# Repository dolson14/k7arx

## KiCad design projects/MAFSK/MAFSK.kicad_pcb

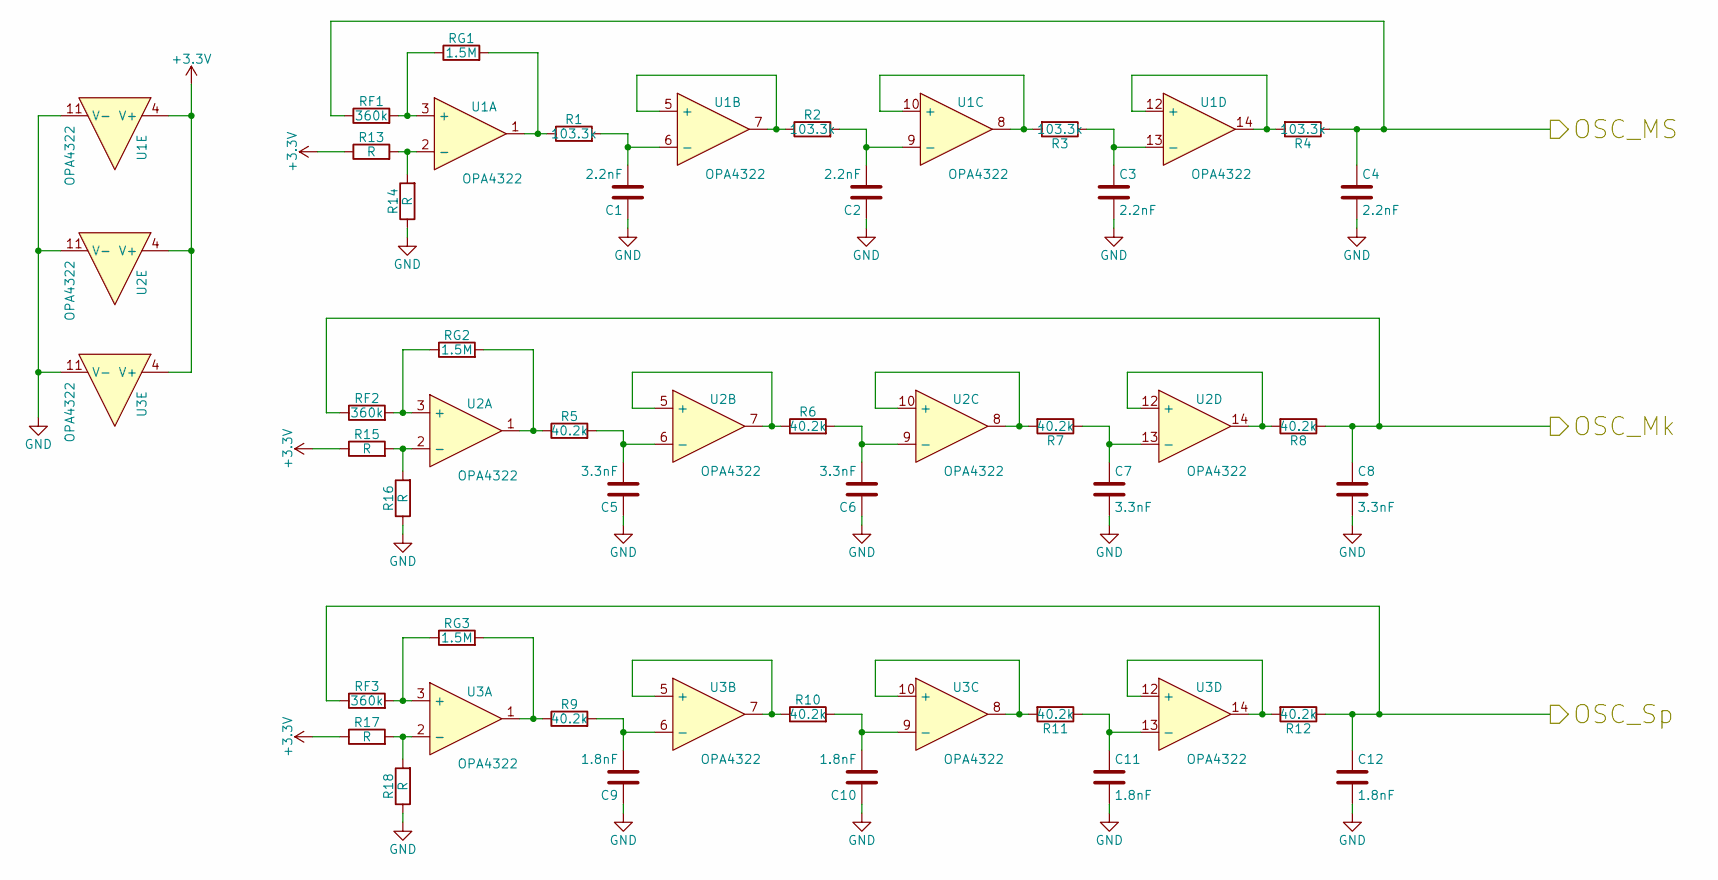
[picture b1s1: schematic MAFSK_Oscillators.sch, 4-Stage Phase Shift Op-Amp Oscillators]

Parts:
C1, C2, C3, C4: 2.2nF; C_1206_HandSoldering
C5, C6, C7, C8: 3.3nF; C_1206_HandSoldering
C9, C10, C11, C12: 1.8nF; C_1206_HandSoldering
R1, R2, R3, R4: 103.3k; R_1206_HandSoldering
R5, R6, R7, R8, R9, R10, R11, R12: 40.2k; R_1206_HandSoldering
R13, R14, R15, R16, R17, R18: R; R_1206_HandSoldering
RF1, RF2, RF3: 360k; R_1206_HandSoldering
RG1, RG2, RG3: 1.5M; R_1206_HandSoldering
U1, U2, U3: OPA4322; PW-14

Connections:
+3V3: R13.1, R15.1, R17.1, U1.4 (V+), U2.4 (V+), U3.4 (V+); also elsewhere on the board
/Oscillators/OSC_MS: C4.1, R4.1, RF1.1; also elsewhere on the board
/Oscillators/OSC_Mk: C8.1, R8.1, RF2.1; also elsewhere on the board
/Oscillators/OSC_Sp: C12.1, R12.1, RF3.1; also elsewhere on the board
GND: C1.1, C2.1, C3.2, C4.2, C5.1, C6.1, C7.2, C8.2, C9.1, C10.1, C11.2, C12.2, R14.1, R16.1, R18.1, U1.11 (V-), U2.11 (V-), U3.11 (V-); also elsewhere on the board
unnamed: C1.2, R1.2, U1.6 (-)
unnamed: C2.2, R2.2, U1.9 (-)
unnamed: C3.1, R3.1, U1.13 (-)
unnamed: C5.2, R5.2, U2.6 (-)
unnamed: C6.2, R6.2, U2.9 (-)
unnamed: C7.1, R7.1, U2.13 (-)
unnamed: C9.2, R9.2, U3.6 (-)
unnamed: C10.2, R10.2, U3.9 (-)
unnamed: C11.1, R11.1, U3.13 (-)
unnamed: R1.1, RG1.2, U1.1
unnamed: R2.1, U1.5 (+), U1.7
unnamed: R3.2, U1.8, U1.10 (+)
unnamed: R4.2, U1.12 (+), U1.14
unnamed: R5.1, RG2.2, U2.1
unnamed: R6.1, U2.5 (+), U2.7
unnamed: R7.2, U2.8, U2.10 (+)
unnamed: R8.2, U2.12 (+), U2.14
unnamed: R9.1, RG3.2, U3.1
unnamed: R10.1, U3.5 (+), U3.7
unnamed: R11.2, U3.8, U3.10 (+)
unnamed: R12.2, U3.12 (+), U3.14
unnamed: R13.2, R14.2, U1.2 (-)
unnamed: R15.2, R16.2, U2.2 (-)
unnamed: R17.2, R18.2, U3.2 (-)
unnamed: RF1.2, RG1.1, U1.3 (+)
unnamed: RF2.2, RG2.1, U2.3 (+)
unnamed: RF3.2, RG3.1, U3.3 (+)

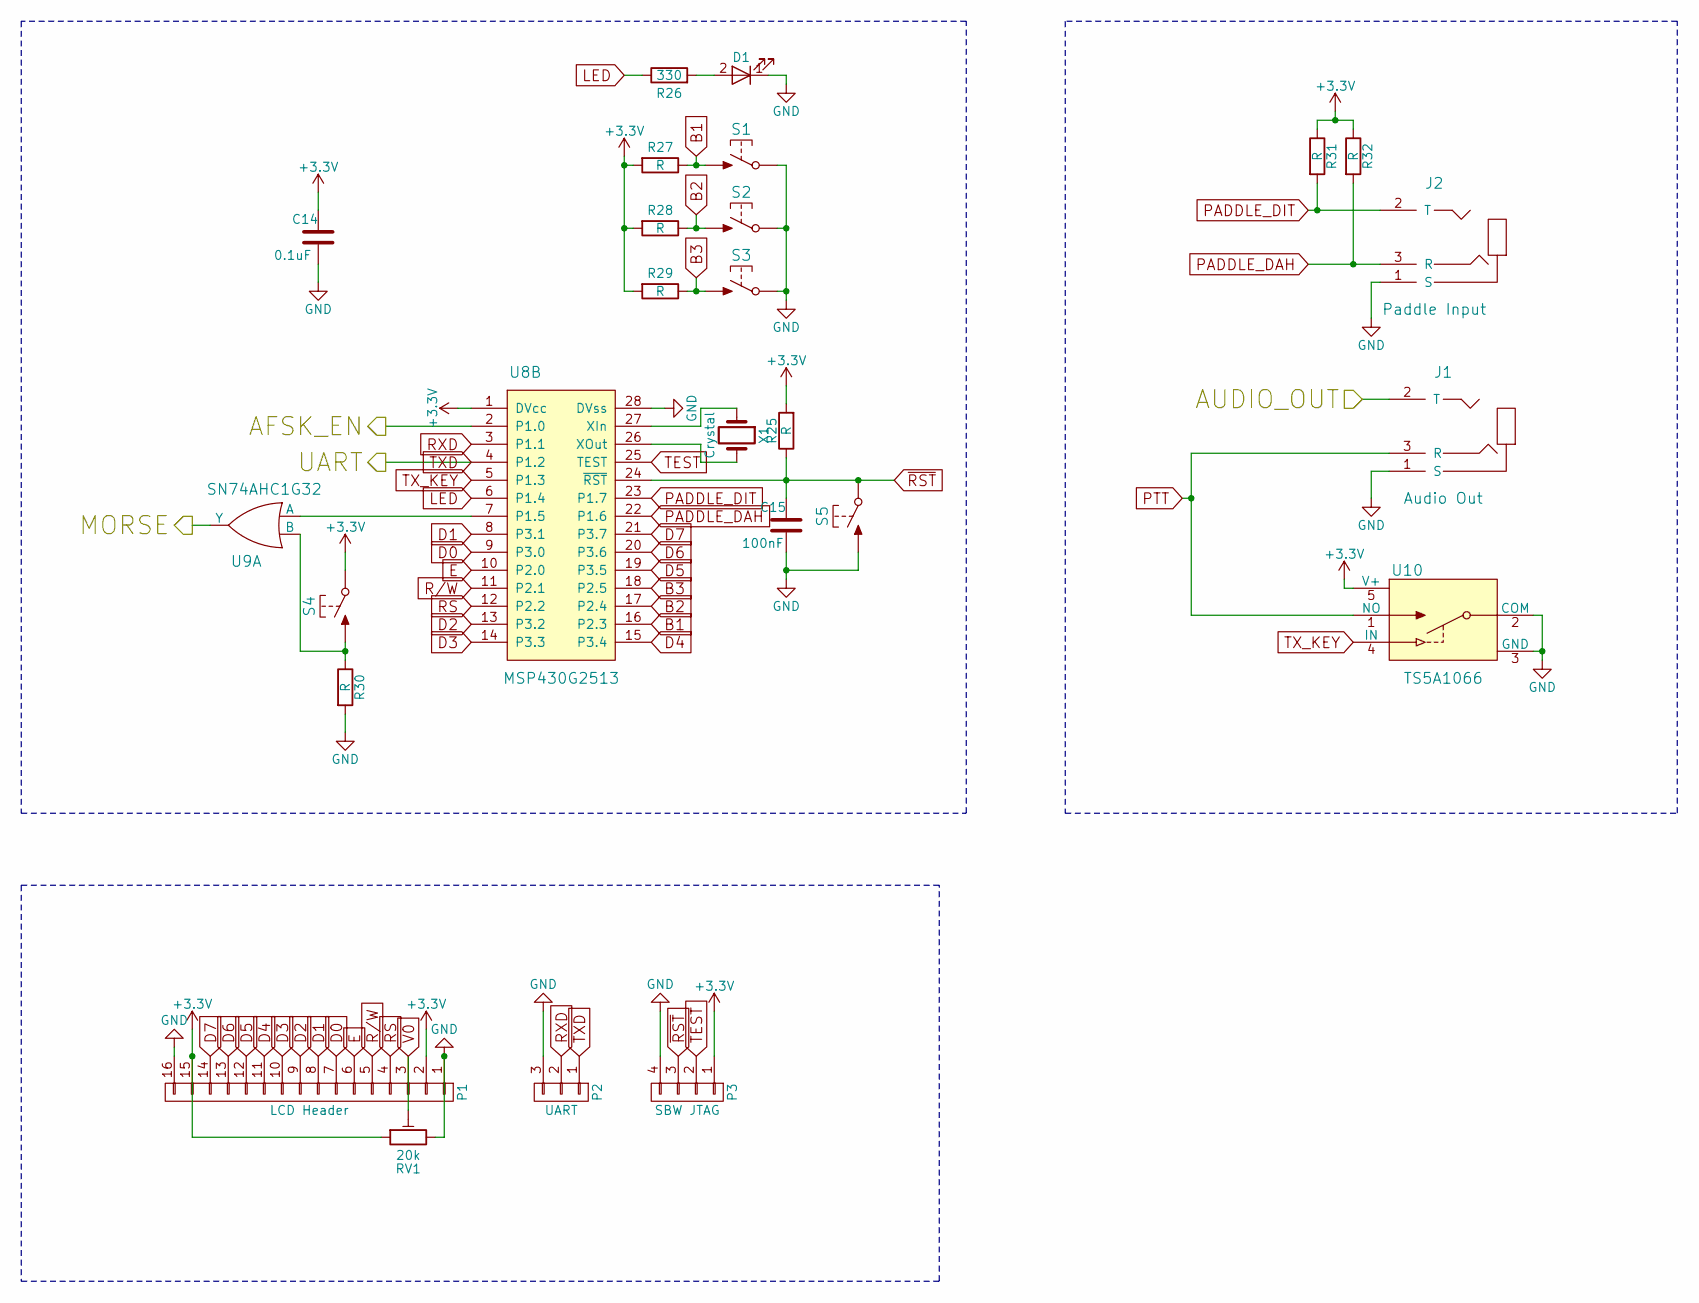
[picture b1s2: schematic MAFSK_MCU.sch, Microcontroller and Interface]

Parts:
C14: 0.1uF; C_1206_HandSoldering
C15: 100nF; C_1206_HandSoldering
D1: LED; LED-0805
J1: Audio Out; Jack-TRS-SJ1-3523N
J2: Paddle Input; Jack-TRS-SJ1-3523N
P1: LCD Header; LCD-1602A
P2: UART; Pin_Header_Straight_1x03
P3: SBW JTAG; Pin_Header_Straight_1x04
R25, R27, R28, R29, R30, R31, R32: R; R_1206_HandSoldering
R26: 330; R_1206_HandSoldering
RV1: 20k; POT-3352T
S1, S2, S3, S4: TactileSwitch_NO; SPST-D6xxx
S5: TactileSwitch_NO; SPST-EVQ2
U8: MSP430G2513; PW-28
U9: SN74AHC1G32; DBV
U10: TS5A1066; DBV
X1: Crystal; XTAL-CMR200T

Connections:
+3V3: C14.1, P1.2, P1.15, P3.1, R25.2, R27.2, R28.2, R29.2, R31.1, R32.1, RV1.1, S4.2 (COM), U8.1 (DVcc), U10.5 (V+); also elsewhere on the board
/Microcontroller/AFSK_EN: U8.2 (P1.0); also elsewhere on the board
/Microcontroller/AUDIO_OUT: J1.2 (T); also elsewhere on the board
/Microcontroller/MORSE: U9.4 (Y); also elsewhere on the board
B1: R27.1, S1.1 (NO), U8.16 (~RST)
B2: R28.1, S2.1 (NO), U8.17 (TEST)
B3: R29.1, S3.1 (NO), U8.18 (XOut)
D0: P1.7, U8.9 (P2.1)
D1: P1.8, U8.8 (P2.0)
D2: P1.9, U8.13 (P2.5)
D3: P1.10, U8.14 (P1.6)
D4: P1.11, U8.15 (P1.7)
D5: P1.12, U8.19 (XIn)
D6: P1.13, U8.20 (DVss)
D7: P1.14, U8.21 (P3.7)
E: P1.6, U8.10 (P2.2)
GND: C14.2, C15.2, D1.1 (K), J1.1 (S), J2.1 (S), P1.1, P1.16, P2.3, P3.4, R30.2, RV1.3, S1.2 (COM), S2.2 (COM), S3.2 (COM), S5.1 (NO), U8.28 (DVss), U10.2 (COM), U10.3 (GND); also elsewhere on the board
LED: R26.1, U8.6 (P1.4)
unnamed: D1.2 (A), R26.2
unnamed: R30.1, S4.1 (NO), U9.2 (B)
unnamed: U8.7 (P1.5), U9.1 (A)
unnamed: U8.26 (XOut), X1.2
unnamed: U8.27 (XIn), X1.1
PADDLE_DAH: J2.3 (R), R32.2, U8.22 (P1.6)
PADDLE_DIT: J2.2 (T), R31.2, U8.23 (P1.7)
PTT: J1.3 (R), U10.1 (NO)
R/W: P1.5, U8.11 (P2.3)
RS: P1.4, U8.12 (P2.4)
RXD: P2.2, U8.3 (P1.1)
TEST: P3.2, U8.25 (TEST)
TXD: P2.1, U8.4 (P1.2); also elsewhere on the board
TX_KEY: U8.5 (P1.3), U10.4 (IN)
V0: P1.3, RV1.2
~RST: C15.1, P3.3, R25.1, S5.2 (COM), U8.24 (~RST)

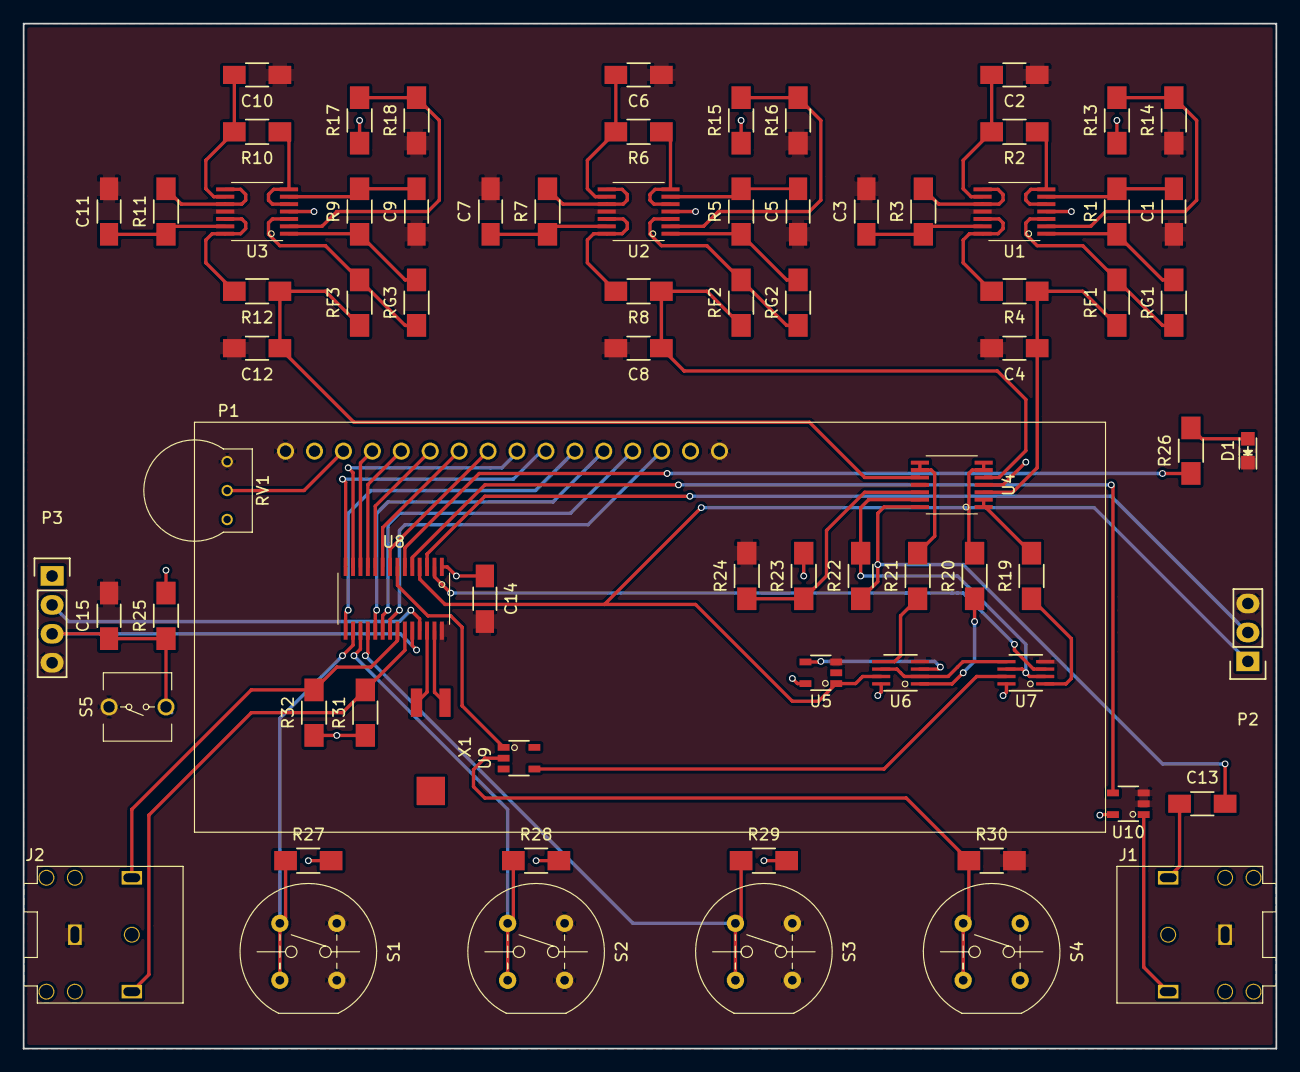
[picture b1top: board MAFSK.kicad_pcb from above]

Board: 2 copper layers, 110.0 x 90.0 mm, 76 parts (0 on the bottom side), 75 nets.

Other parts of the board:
C13: C; C_1206_HandSoldering
R19, R20, R21, R22, R23, R24: R; R_1206_HandSoldering
U4: OPA4322; PW-14
U5: SN74AHC1G14; DBV
U6, U7: TS5A2066; DCT

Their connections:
+3V3: R23.2, U4.4, U5.5, U6.8, U7.8; also elsewhere on the board
/Microcontroller/AFSK_EN: U7.3; also elsewhere on the board
/Microcontroller/AUDIO_OUT: C13.1; also elsewhere on the board
/Microcontroller/MORSE: U7.7; also elsewhere on the board
/Oscillators/OSC_MS: U4.3; also elsewhere on the board
/Oscillators/OSC_Mk: U4.5; also elsewhere on the board
/Oscillators/OSC_Sp: U4.10; also elsewhere on the board
GND: R24.2, U4.11, U5.3, U6.4, U7.4; also elsewhere on the board
unnamed: C13.2, R22.1, U4.14
unnamed: R19.1, U7.1
unnamed: R19.2, U4.1, U4.2
unnamed: R20.1, U6.1
unnamed: R20.2, U4.6, U4.7
unnamed: R21.1, U6.5
unnamed: R21.2, U4.8, U4.9
unnamed: R22.2, U4.13, U7.2, U7.6
unnamed: R23.1, R24.1, U4.12
unnamed: U5.4, U6.3
unnamed: U6.2, U6.6, U7.5
TXD: U5.1, U6.7; also elsewhere on the board

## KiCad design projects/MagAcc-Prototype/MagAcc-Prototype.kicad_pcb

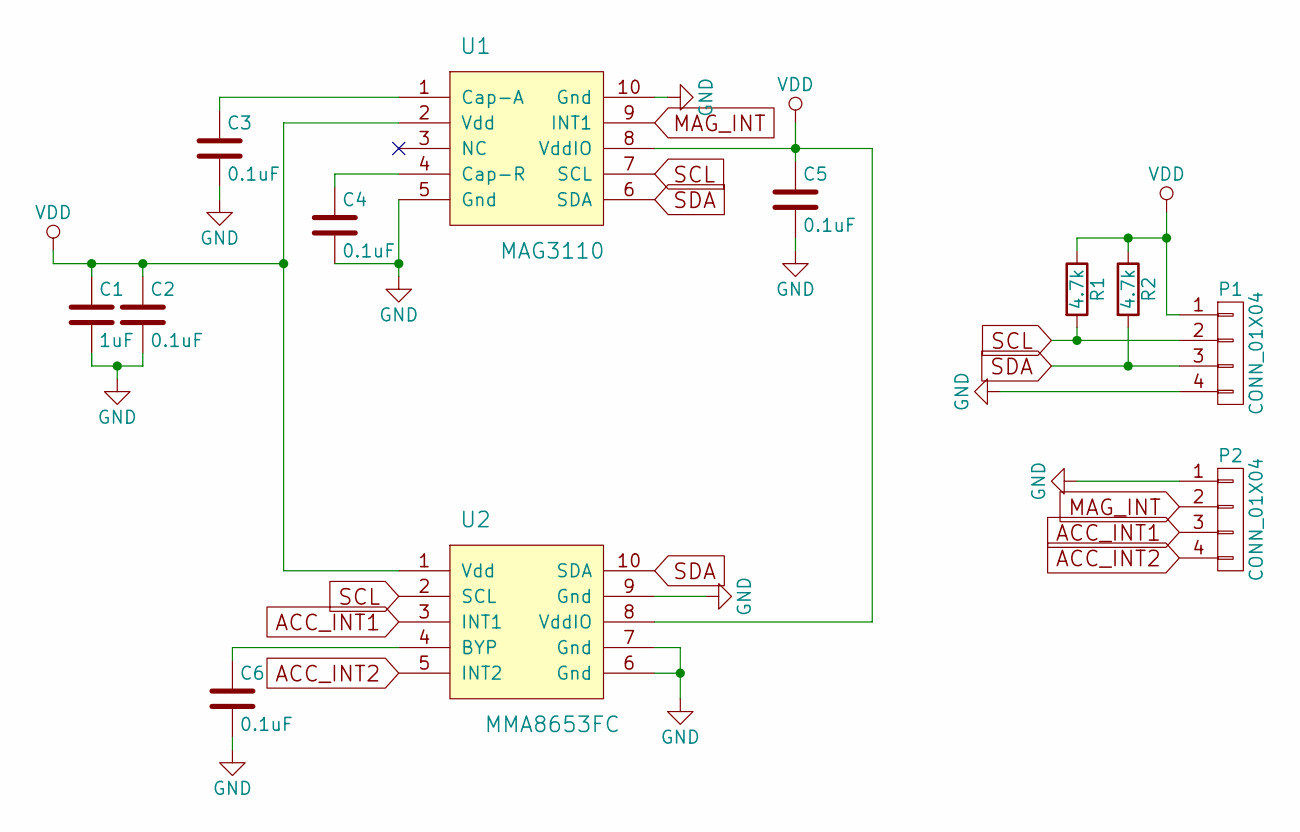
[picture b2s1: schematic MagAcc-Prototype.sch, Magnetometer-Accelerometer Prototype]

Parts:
C1: 1uF; C_1206_HandSoldering
C2, C3, C4, C5, C6: 0.1uF; C_1206_HandSoldering
P1, P2: CONN_01X04; Pin_Header_Straight_1x04
R1, R2: 4.7k; R_1206_HandSoldering
U1: MAG3110; DFN-10-HS
U2: MMA8653FC; DFN-10-HS

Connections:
ACC_INT1: P2.3, U2.3 (INT1)
ACC_INT2: P2.4, U2.5 (INT2)
GND: C1.2, C2.2, C3.2, C4.2, C5.2, C6.2, P1.4, P2.1, U1.5 (Gnd), U1.10 (Gnd), U2.6 (Gnd), U2.7 (Gnd), U2.9 (Gnd)
MAG_INT: P2.2, U1.9 (INT1)
unnamed: C3.1, U1.1 (Cap-A)
unnamed: C4.1, U1.4 (Cap-R)
unnamed: C6.1, U2.4 (BYP)
SCL: P1.2, R1.2, U1.7 (SCL), U2.2 (SCL)
SDA: P1.3, R2.2, U1.6 (SDA), U2.10 (SDA)
VDD: C1.1, C2.1, C5.1, P1.1, R1.1, R2.1, U1.2 (Vdd), U1.8 (VddIO), U2.1 (Vdd), U2.8 (VddIO)

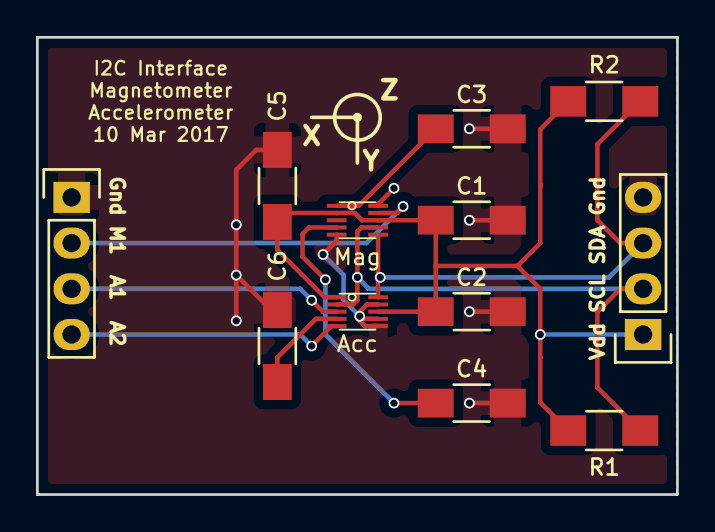
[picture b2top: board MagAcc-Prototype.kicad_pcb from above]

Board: 2 copper layers, 35.6 x 25.4 mm, 12 parts (0 on the bottom side), 10 nets.

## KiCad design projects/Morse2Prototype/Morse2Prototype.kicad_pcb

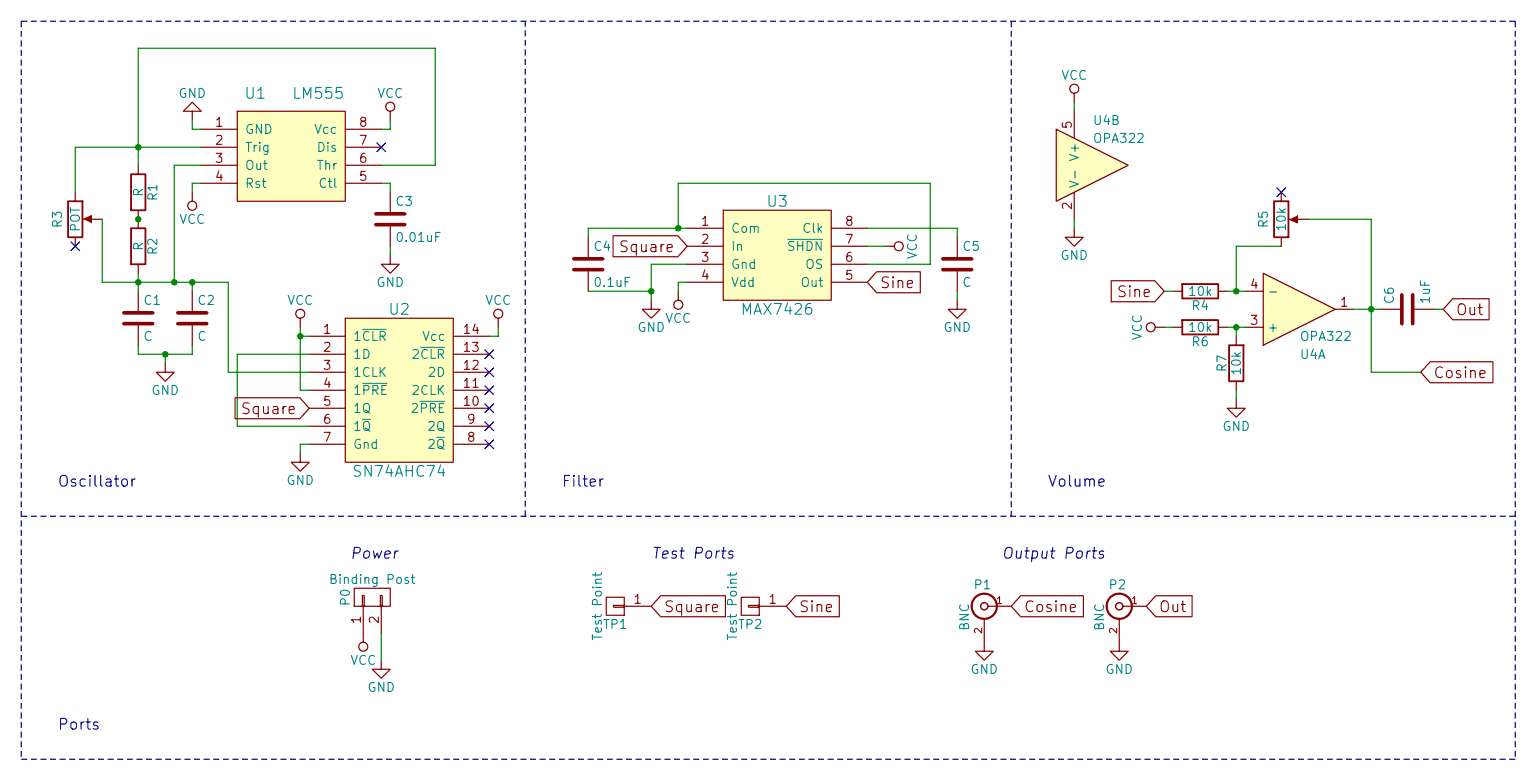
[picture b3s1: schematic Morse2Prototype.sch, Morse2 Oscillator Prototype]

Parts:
C1, C2, C5: C; C_Disc_D6_P5
C3: 0.01uF; C_Disc_D6_P5
C4: 0.1uF; C_Disc_D6_P5
C6: 1uF; C_Radial_D5_L11_P2.5
P0: Binding Post; Pin_Header_Straight_1x02
P1, P2: BNC; SMA_Board_Edge
R1, R2: R; Resistor_Horizontal_RM10mm
R3: POT; Resistor_Horizontal_RM10mm
R4, R5, R6, R7: 10k; Resistor_Horizontal_RM10mm
TP1, TP2: Test Point; Pin_Header_Straight_1x01
U1: LM555; DIP-8_W7.62mm_LongPads
U2: SN74AHC74; DIP-14_W7.62mm_LongPads
U3: MAX7426; DIP-8_W7.62mm_LongPads
U4: OPA322; DIP-8_W7.62mm_LongPads

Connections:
Cosine: C6.1, P1.1 (In), R5.2, U4.1
GND: C1.2, C2.2, C3.2, C4.2, C5.2, P0.2, P1.2 (Ext), P2.2 (Ext), R7.1, U1.1 (GND), U2.7 (Gnd), U3.3 (Gnd), U4.2 (V-)
unnamed: C1.1, C2.1, R2.2, R3.2, U1.3 (Out), U2.3 (1CLK)
unnamed: C3.1, U1.5 (Ctl)
unnamed: C4.1, U3.1 (Com), U3.6 (OS)
unnamed: C5.1, U3.8 (Clk)
unnamed: R1.1, R3.1, U1.2 (Trig), U1.6 (Thr)
unnamed: R1.2, R2.1
unnamed: R4.1, R5.1, U4.4 (-)
unnamed: R6.1, R7.2, U4.3 (+)
unnamed: U2.2 (1D), U2.6 (1~Q)
Out: C6.2, P2.1 (In)
Sine: R4.2, TP2.1, U3.5 (Out)
Square: TP1.1, U2.5 (1Q), U3.2 (In)
VCC: P0.1, R6.2, U1.4 (Rst), U1.8 (Vcc), U2.1 (1~CLR), U2.4 (1~PRE), U2.14 (Vcc), U3.4 (Vdd), U3.7 (~SHDN), U4.5 (V+)

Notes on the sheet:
Oscillator
Filter
Volume
Ports
Test Ports
Output Ports
Power

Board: 2 copper layers, 22 parts (0 on the bottom side), 15 nets, no tracks yet.

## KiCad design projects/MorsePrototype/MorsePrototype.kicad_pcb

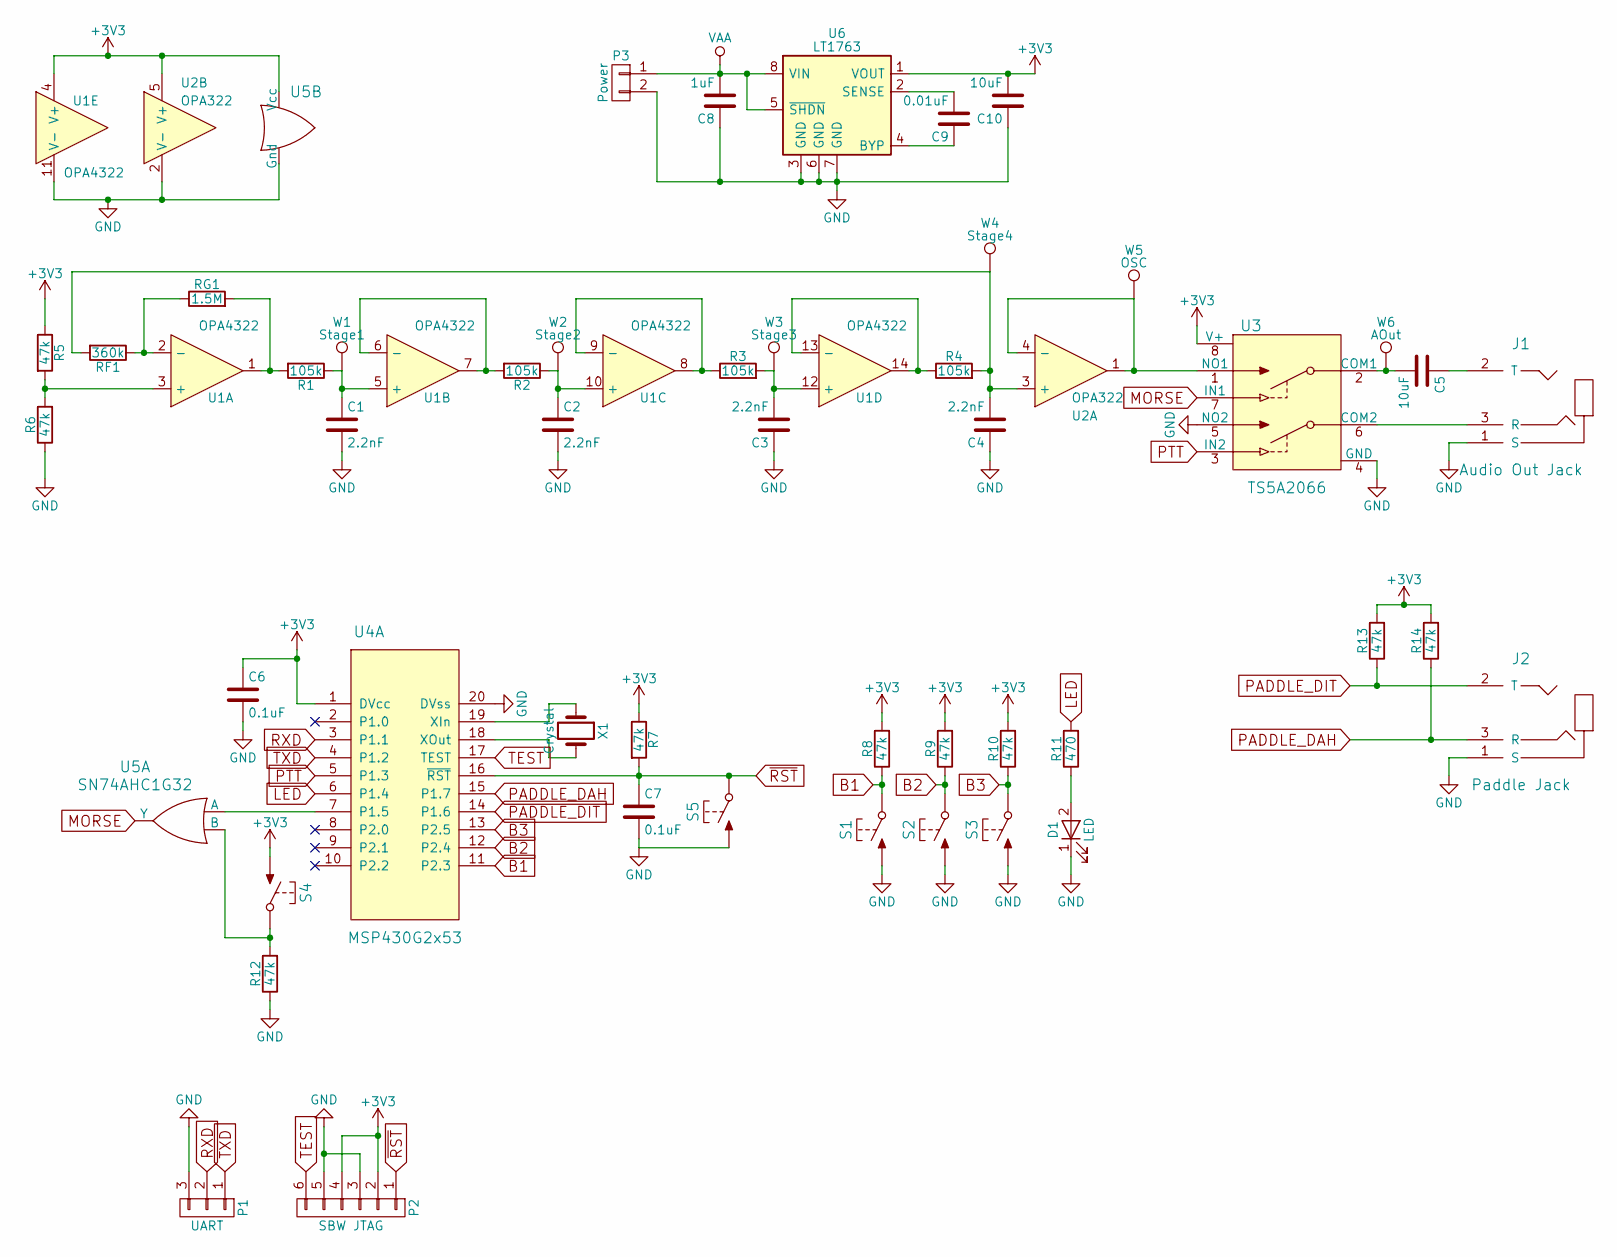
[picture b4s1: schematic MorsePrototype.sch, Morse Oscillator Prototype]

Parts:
C1, C2, C3, C4: 2.2nF; C_0805_HandSoldering
C5, C10: 10uF; C_0805_HandSoldering
C6, C7: 0.1uF; C_0805_HandSoldering
C8: 1uF; C_0805_HandSoldering
C9: 0.01uF; C_0805_HandSoldering
D1: LED; LED_0805
J1: Audio Out Jack; Jack-TRS-SJ1-3523N
J2: Paddle Jack; Jack-TRS-SJ1-3523N
P1: UART; Pin_Header_Straight_1x03
P2: SBW JTAG; Tag-Connect_TC2030-NL
P3: Power; Pin_Header_Straight_1x02
R1, R2, R3, R4: 105k; R_0805_HandSoldering
R5, R6, R7, R8, R9, R10, R12, R13, R14: 47k; R_0805_HandSoldering
R11: 470; R_0805_HandSoldering
RF1: 360k; R_0805_HandSoldering
RG1: 1.5M; R_0805_HandSoldering
S1, S2, S3, S4, S5: TactileSwitch_NO; SPST-EVQ2
U1: OPA4322; PW-14
U2: OPA322; DBV
U3: TS5A2066; DCT
U4: MSP430G2x53; PW-20
U5: SN74AHC1G32; DBV
U6: LT1763; SOIC-8-N
W1: Stage1; Test_Point
W2: Stage2; Test_Point
W3: Stage3; Test_Point
W4: Stage4; Test_Point
W5: OSC; Test_Point
W6: AOut; Test_Point
X1: Crystal; XTAL-CMR200T

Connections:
+3V3: C6.1, C10.2, P2.2, P2.4, R5.1, R7.1, R8.2, R9.2, R10.2, R13.2, R14.2, S4.1 (NO), U1.4 (V+), U2.5 (V+), U3.8 (V+), U4.1 (DVcc), U5.5 (Vcc), U6.1 (VOUT)
B1: R8.1, S1.2 (COM), U4.11 (P2.3)
B2: R9.1, S2.2 (COM), U4.12 (P2.4)
B3: R10.1, S3.2 (COM), U4.13 (P2.5)
GND: C1.2, C2.2, C3.1, C4.1, C6.2, C7.2, C8.1, C10.1, D1.1 (K), J1.1 (S), J2.1 (S), P1.3, P2.3, P2.5, P3.2, R6.1, R12.1, S1.1 (NO), S2.1 (NO), S3.1 (NO), S5.1 (NO), U1.11 (V-), U2.2 (V-), U3.4 (GND), U3.5 (NO2), U4.20 (DVss), U5.3 (Gnd), U6.3 (GND), U6.6 (GND), U6.7 (GND)
LED: R11.2, U4.6 (P1.4)
MORSE: U3.7 (IN1), U5.4 (Y)
unnamed: C1.1, R1.1, U1.5 (+), W1.1
unnamed: C2.1, R2.1, U1.10 (+), W2.1
unnamed: C3.2, R3.2, U1.12 (+), W3.1
unnamed: C4.2, R4.2, RF1.2, U2.3 (+), W4.1
unnamed: C5.1, J1.2 (T)
unnamed: C5.2, U3.2 (COM1), W6.1
unnamed: C9.1, U6.4 (BYP)
unnamed: C9.2, U6.2 (SENSE)
unnamed: D1.2 (A), R11.1
unnamed: J1.3 (R), U3.6 (COM2)
unnamed: R1.2, RG1.2, U1.1
unnamed: R2.2, U1.6 (-), U1.7
unnamed: R3.1, U1.8, U1.9 (-)
unnamed: R4.1, U1.13 (-), U1.14
unnamed: R5.2, R6.2, U1.3 (+)
unnamed: R12.2, S4.2 (COM), U5.2 (B)
unnamed: RF1.1, RG1.1, U1.2 (-)
unnamed: U2.1, U2.4 (-), U3.1 (NO1), W5.1
unnamed: U4.7 (P1.5), U5.1 (A)
unnamed: U4.18 (XOut), X1.2
unnamed: U4.19 (XIn), X1.1
PADDLE_DAH: J2.3 (R), R14.1, U4.15 (P1.7)
PADDLE_DIT: J2.2 (T), R13.1, U4.14 (P1.6)
PTT: U3.3 (IN2), U4.5 (P1.3)
RXD: P1.2, U4.3 (P1.1)
TEST: P2.6, U4.17 (TEST)
TXD: P1.1, U4.4 (P1.2)
VAA: C8.2, P3.1, U6.5 (~SHDN), U6.8 (VIN)
~RST: C7.1, P2.1, R7.2, S5.2 (COM), U4.16 (~RST)

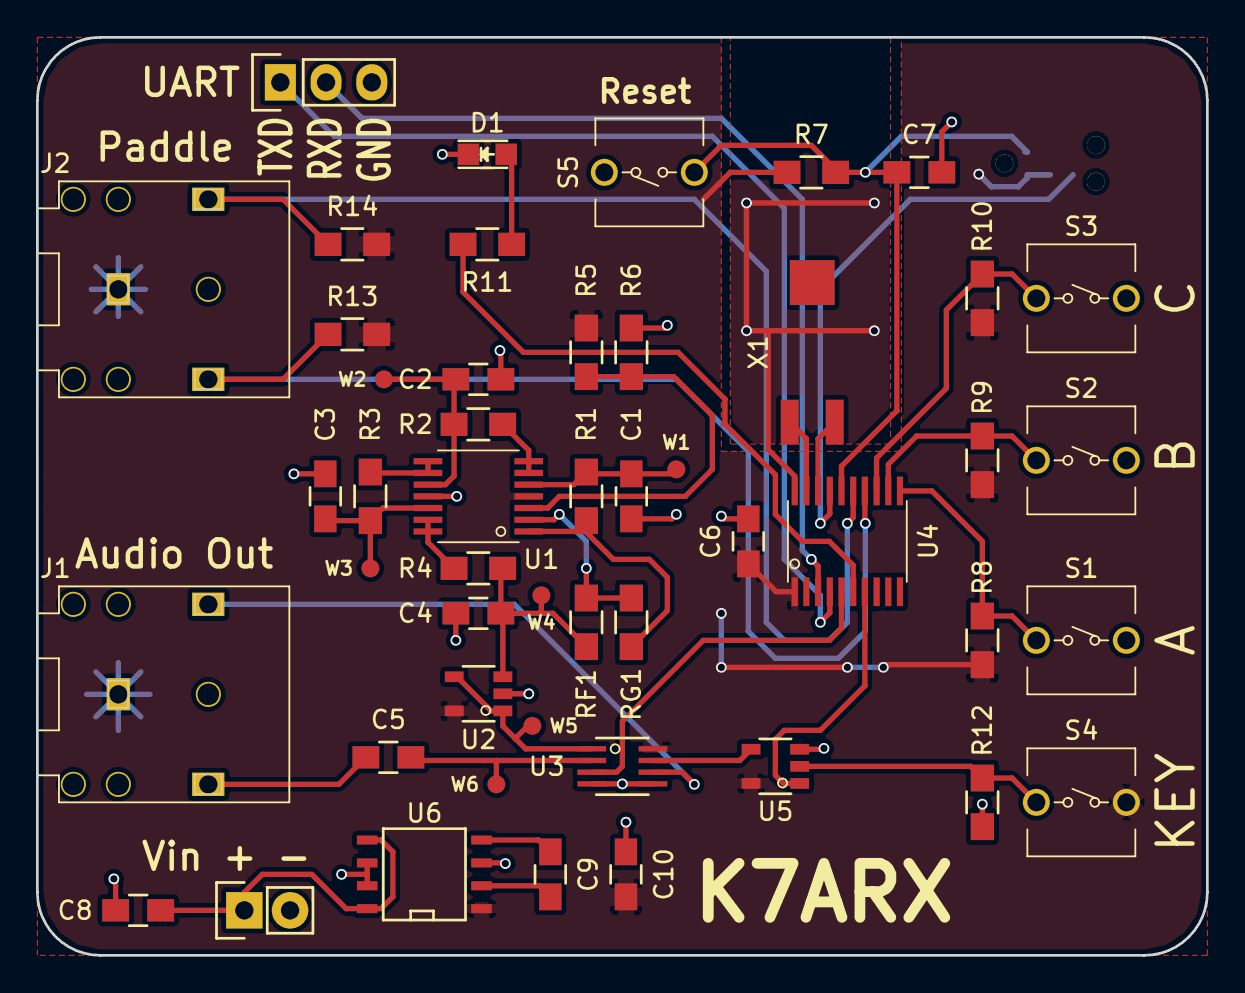
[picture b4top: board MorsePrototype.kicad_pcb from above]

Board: 2 copper layers, 65.0 x 51.0 mm, 50 parts (1 on the bottom side), 36 nets.

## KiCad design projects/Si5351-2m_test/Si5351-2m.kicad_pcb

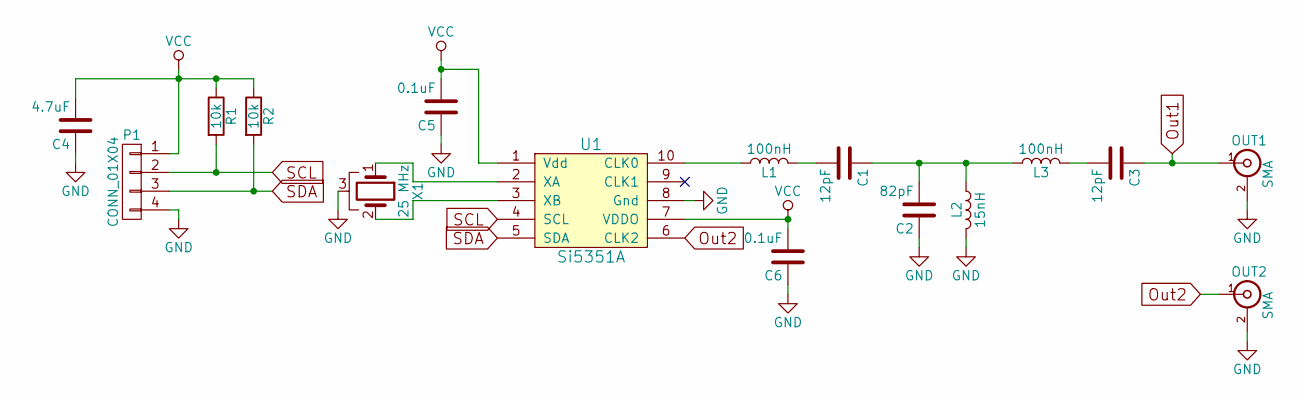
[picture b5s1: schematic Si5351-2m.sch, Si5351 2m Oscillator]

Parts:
C1, C3: 12pF; C_0603_HandSoldering
C2: 82pF; C_0603_HandSoldering
C4: 4.7uF; C_0603_HandSoldering
C5, C6: 0.1uF; C_0603_HandSoldering
L1, L3: 100nH; C_0603_HandSoldering
L2: 15nH; C_0603_HandSoldering
OUT1, OUT2: SMA; SMA_Board_Edge
P1: CONN_01X04; Pin_Header_Straight_1x04
R1, R2: 10k; R_0603_HandSoldering
U1: Si5351A; MSOP-10
X1: 25 MHz; Crystal_SMD_5032_4Pads

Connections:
GND: C2.1, C4.1, C5.1, C6.1, L2.2, OUT1.2 (Ext), OUT2.2 (Ext), P1.4, U1.8 (Gnd), X1.3
unnamed: C1.1, C2.2, L2.1, L3.1
unnamed: C1.2, L1.2
unnamed: C3.2, L3.2
unnamed: L1.1, U1.10 (CLK0)
unnamed: U1.2 (XA), X1.1
unnamed: U1.3 (XB), X1.2
Out1: C3.1, OUT1.1 (In)
Out2: OUT2.1 (In), U1.6 (CLK2)
SCL: P1.2, R1.2, U1.4 (SCL)
SDA: P1.3, R2.2, U1.5 (SDA)
VCC: C4.2, C5.2, C6.2, P1.1, R1.1, R2.1, U1.1 (Vdd), U1.7 (VDDO)

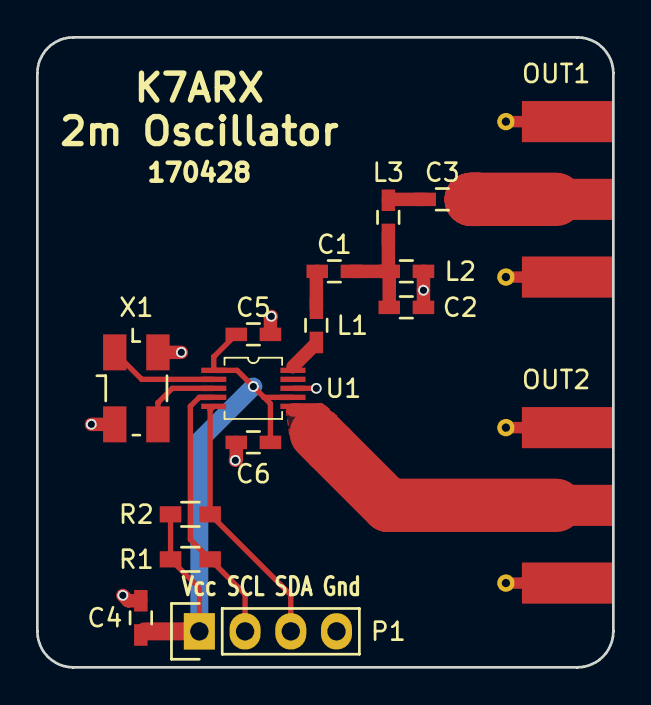
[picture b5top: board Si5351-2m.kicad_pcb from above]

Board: 2 copper layers, 32.0 x 35.0 mm, 16 parts (0 on the bottom side), 12 nets.

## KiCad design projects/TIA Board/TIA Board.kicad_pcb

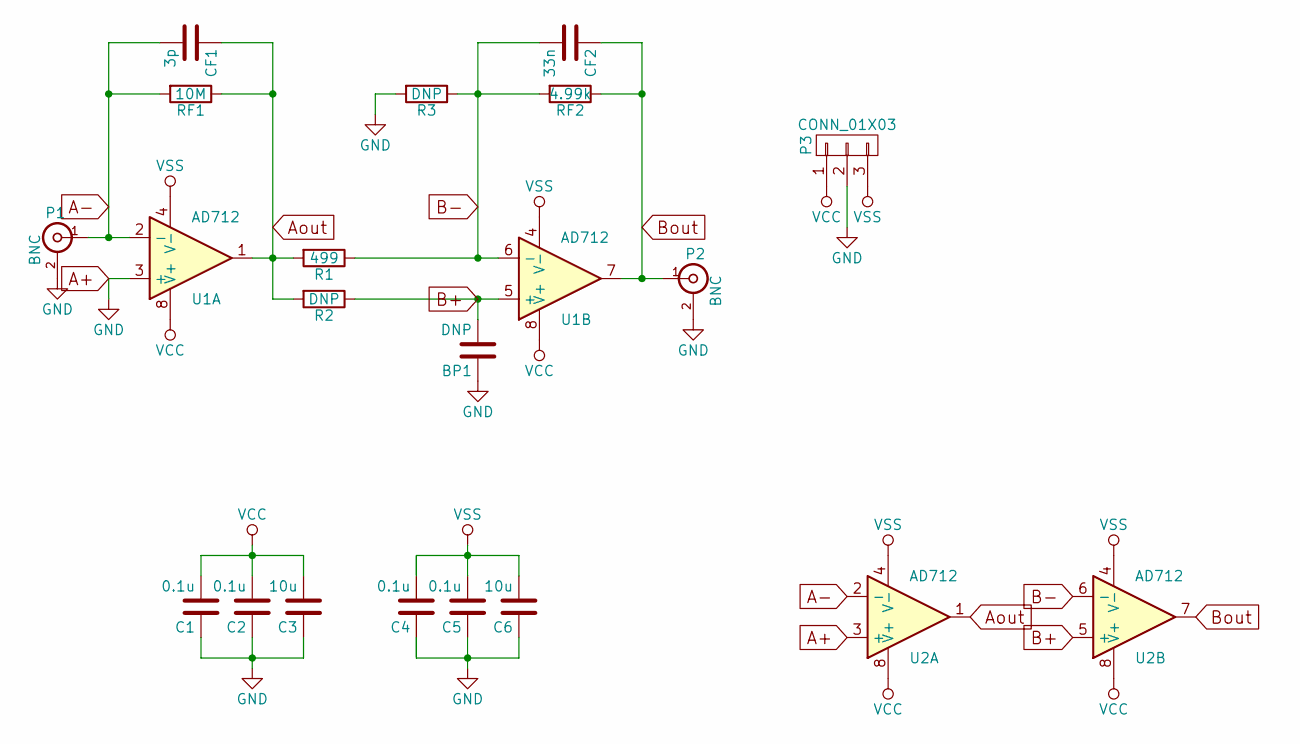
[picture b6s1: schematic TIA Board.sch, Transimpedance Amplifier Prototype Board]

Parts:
BP1: DNP; Resistor_SMD+THTuniversal_0805to1206_RM10_HandSoldering
C1, C2, C4, C5: 0.1u; Resistor_SMD+THTuniversal_0805to1206_RM10_HandSoldering
C3, C6: 10u; Resistor_SMD+THTuniversal_0805to1206_RM10_HandSoldering
CF1: 3p; Resistor_SMD+THTuniversal_0805to1206_RM10_HandSoldering
CF2: 33n; Resistor_SMD+THTuniversal_0805to1206_RM10_HandSoldering
P1, P2: BNC; BNC_Panel_Feedthrough
P3: CONN_01X03; Pin_Header_Straight_1x03
R1: 499; Resistor_SMD+THTuniversal_0805to1206_RM10_HandSoldering
R2, R3: DNP; Resistor_SMD+THTuniversal_0805to1206_RM10_HandSoldering
RF1: 10M; Resistor_SMD+THTuniversal_0805to1206_RM10_HandSoldering
RF2: 4.99k; Resistor_SMD+THTuniversal_0805to1206_RM10_HandSoldering
U1: AD712; SOIC-8-N
U2: AD712; PDIP-8

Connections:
A+: BP1.1, C1.1, C2.1, C3.1, C4.1, C5.1, C6.1, P1.2 (Ext), P2.2 (Ext), P3.2, R3.2, U1.3 (+), U2.3 (+)
A-: CF1.2, P1.1 (In), RF1.2, U1.2 (-), U2.2 (-)
Aout: CF1.1, R1.2, R2.2, RF1.1, U1.1, U2.1
B+: BP1.2, R2.1, U1.5 (+), U2.5 (+)
B-: CF2.2, R1.1, R3.1, RF2.2, U1.6 (-), U2.6 (-)
Bout: CF2.1, P2.1 (In), RF2.1, U1.7, U2.7
VCC: C1.2, C2.2, C3.2, P3.1, U1.8 (V+), U2.8 (V+)
VSS: C4.2, C5.2, C6.2, P3.3, U1.4 (V-), U2.4 (V-)

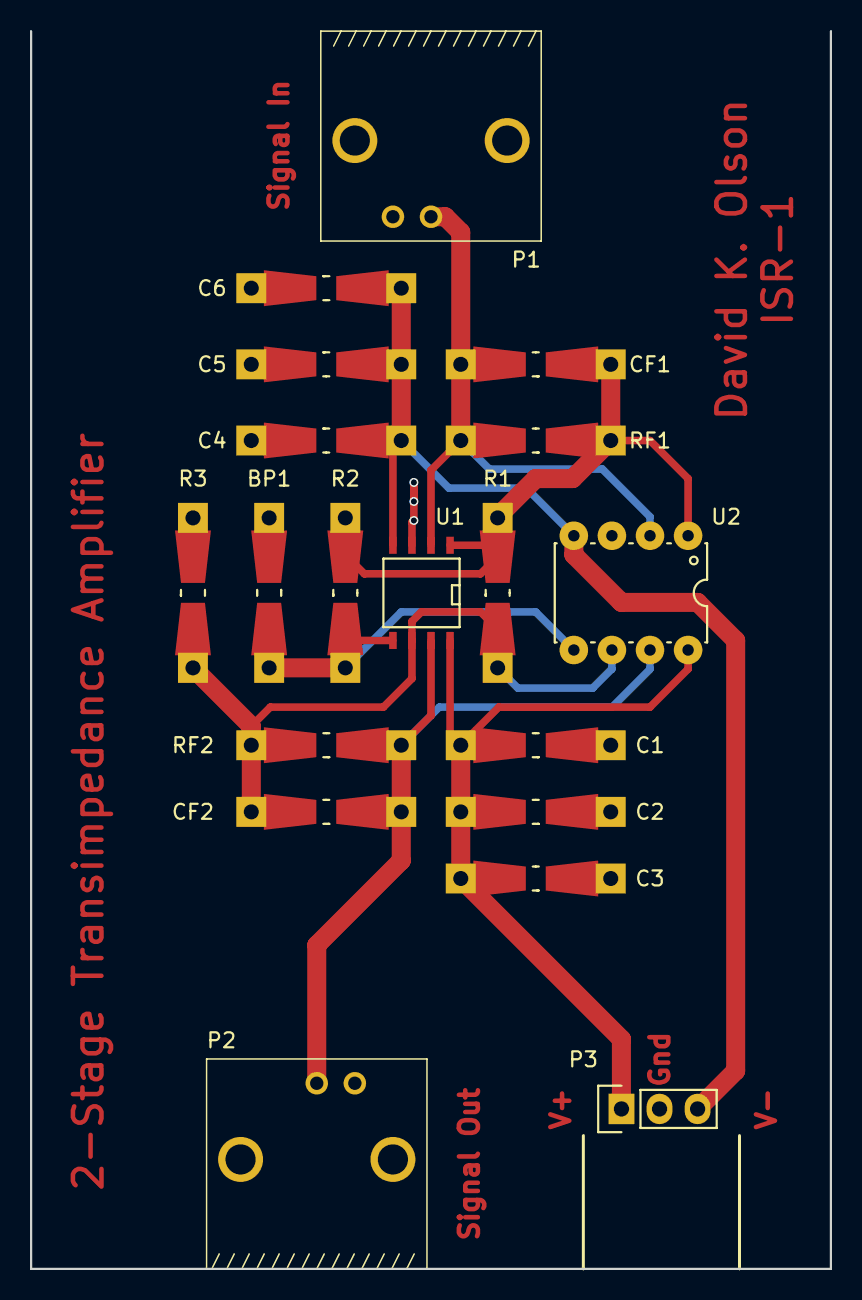
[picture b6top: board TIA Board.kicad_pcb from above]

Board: 2 copper layers, 53.3 x 82.6 mm, 19 parts (0 on the bottom side), 8 nets.
